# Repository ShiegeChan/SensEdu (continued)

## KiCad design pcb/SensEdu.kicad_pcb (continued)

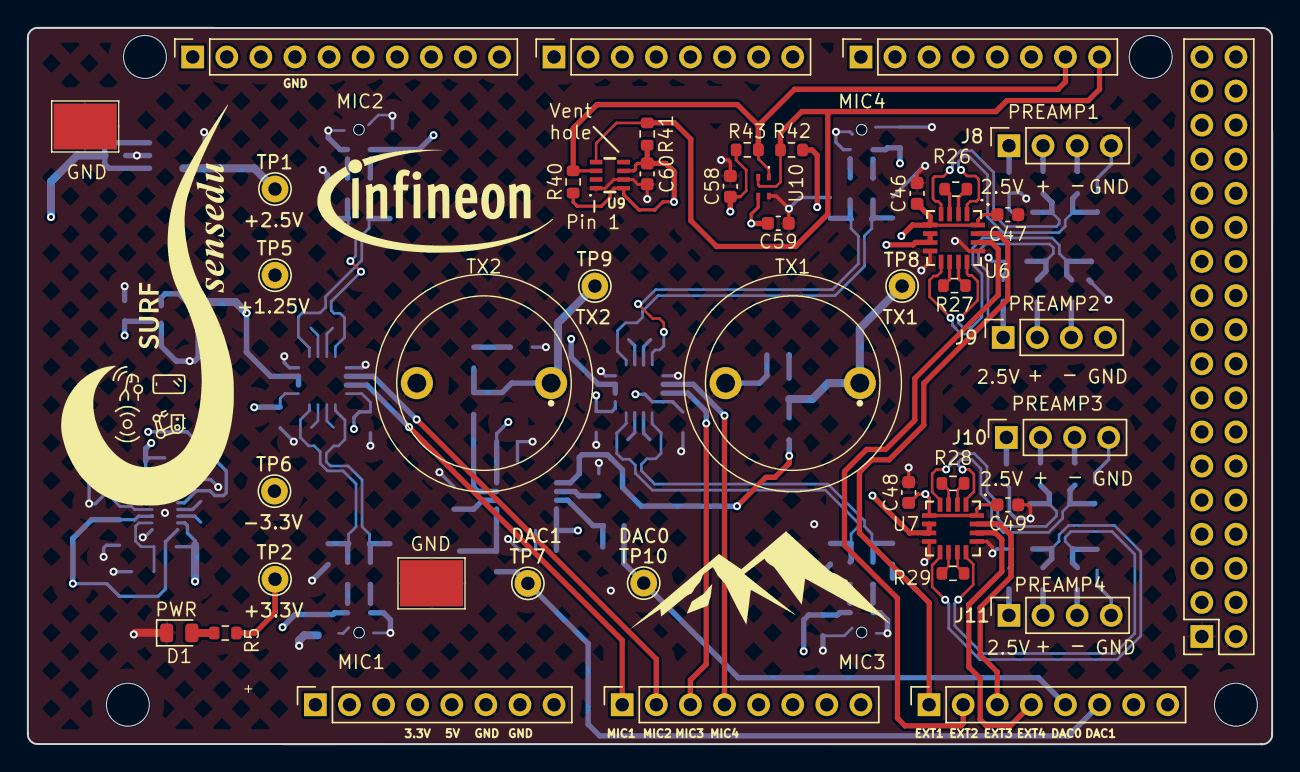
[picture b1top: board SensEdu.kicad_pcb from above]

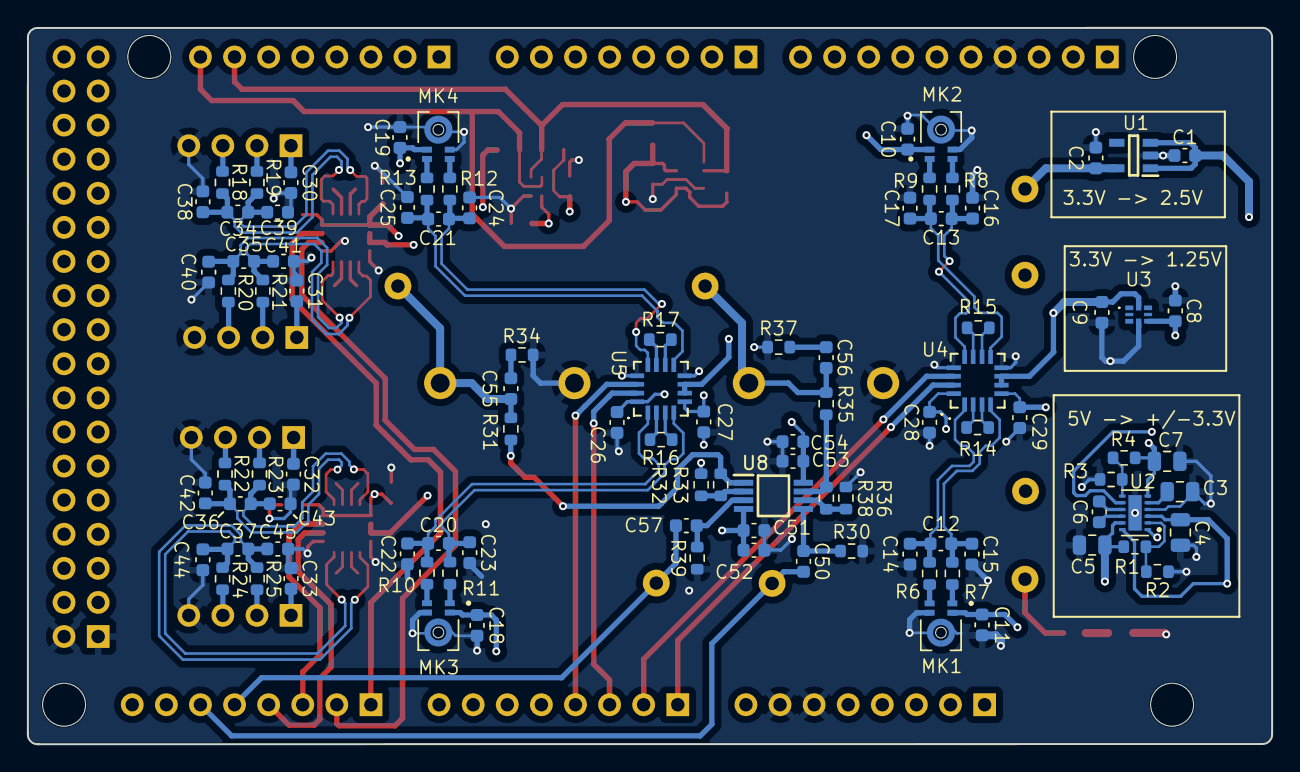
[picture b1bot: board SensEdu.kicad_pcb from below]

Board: 4 copper layers, 92.7 x 53.4 mm, 145 parts (97 on the bottom side), 83 nets.

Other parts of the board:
MH1, MH2, MH5, MH6: MountingHole_3.2mm

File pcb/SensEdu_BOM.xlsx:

Reference | Value | Footprint | Qty | DNP | Price (per 10xQty) | Total Price | Part Number | Note | Link
C1,C2,C8,C9,C26,C27,C28,C29,C46,C47,C48,C49,C51,C54 | 1u | SensEdu:C_0603_1608Metric | 14 |  | 6.5000000000000002E-2 | 0.91 | GCJ188R71E105KA01D | 10%; X7R | https://www.mouser.de/ProductDetail/Murata-Electronics/GCJ18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
C3,C4 | 4.7u | SensEdu:C_0805_2012Metric | 2 |  | 0.13300000000000001 | 0.26600000000000001 | GCJ21BR71C475KA01L | 10%; X7R | https://www.mouser.de/ProductDetail/Murata-Electronics/GCJ21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
C5,C7 | 2.2u | SensEdu:C_0805_2012Metric | 2 |  | 0.04 | 0.08 | CL21B225KAFNNNG | 10%; X7R | https://www.mouser.de/ProductDetail/Samsung-Electro-Mechanic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
C6 | 470n | SensEdu:C_0603_1608Metric | 1 |  | 5.1999999999999998E-2 | 5.1999999999999998E-2 | GRM188R71A474JA61J | 5%; X7R | https://www.mouser.de/ProductDetail/Murata-Electronics/GRM18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
C10,C11,C18,C19,C30,C31,C32,C33,C52,C53,C58,C59,C60 | 100n | SensEdu:C_0603_1608Metric | 13 |  | 5.0000000000000001E-3 | 6.5000000000000002E-2 | CL10B104JB8NNNC | 5%; X7R | https://www.mouser.de/ProductDetail/Samsung-Electro-Mechanic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
C12,C13,C20,C21,C34,C35,C36,C37 | 470p | SensEdu:C_0603_1608Metric | 8 |  | 8.3000000000000004E-2 | 0.66400000000000003 | GCM1885C2A471FA16D | 1%; C0G | https://www.mouser.de/ProductDetail/Murata-Electronics/GCM18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
C14,C15,C16,C17,C22,C23,C24,C25,C38,C39,C40,C41,C42,C43,C44,C45 | 100p | SensEdu:C_0603_1608Metric | 16 |  | 4.1000000000000002E-2 | 0.65600000000000003 | GQM1875C2E101FB12D | 2%; C0G | https://www.mouser.de/ProductDetail/Murata-Electronics/GQM18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
C50,C57 | 1n | SensEdu:C_0603_1608Metric | 2 |  | 5.1999999999999998E-2 | 0.104 | GCM1885C2A102FA16D | 1%; C0G | https://mou.sr/3Q4kneA
C55,C56 | DNI | SensEdu:C_0603_1608Metric | 2 | DNP |  | 0
D1 | LED | SensEdu:LED_0805_2012Metric | 1 |  | 0.126 | 0.126 | 598-8170-107F |  | https://www.mouser.de/ProductDetail/Dialight/598-8170-107F?q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
J1,J3,J4,J5,J6 | 1x8 Housing | SensEdu:PinSocket_1x08_P2.54mm_Vertical | 5 |  | 1.51 | 7.55 | SSQ-108-03-G-S |  | https://www.mouser.de/ProductDetail/Samtec/SSQ-108-03-G-S?qs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
J2 | 1x10 Housing | SensEdu:PinSocket_1x10_P2.54mm_Vertical | 1 |  | 2.2799999999999998 | 2.2799999999999998 | SSQ-110-03-G-S |  | https://www.mouser.de/ProductDetail/Samtec/SSQ-110-03-G-S?qs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
J7 | 2x18 Housing | SensEdu:PinSocket_2x18_P2.54mm_Vertical | 1 | DNP |  | 0
J8,J9,J10,J11 | 1x4 Housing | SensEdu:PinSocket_1x04_P2.54mm_Vertical | 4 |  | 1.1599999999999999 | 4.6399999999999997 | SSW-104-01-G-S |  | https://www.mouser.de/ProductDetail/Samtec/SSW-104-01-G-S?qs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
MK1,MK2,MK3,MK4 | IM73A135V01XTSA1 | SensEdu:MIC_IM73A135V01XTSA1 | 4 |  | 1.41 | 5.64 | IM73A135V01XTSA1 |  | https://mou.sr/4aXaWrH
R1,R4 | 130k | SensEdu:R_0603_1608Metric | 2 |  | 3.9E-2 | 7.8E-2 | ERA-3AED134V | 0.5%; 100mW; 25ppm | https://www.mouser.de/ProductDetail/Panasonic/ERA-3AED134V?q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
R2,R3 | 75k | SensEdu:R_0603_1608Metric | 2 |  | 0.17599999999999999 | 0.35199999999999998 | ERA-3APB753V | 0.1%; 100mW; 15ppm | https://www.mouser.de/ProductDetail/Panasonic/ERA-3APB753V?q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
R5 | 47 | SensEdu:R_0603_1608Metric | 1 |  | 4.5999999999999999E-2 | 4.5999999999999999E-2 | ERA-3AEB470V | 0.1%; 100mW; 25ppm | https://www.mouser.de/ProductDetail/Panasonic/ERA-3AEB470V?q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
R6,R7,R8,R9,R10,R11,R12,R13,R18,R19,R20,R21,R22,R23,R24,R25 | 3.9k | SensEdu:R_0603_1608Metric | 16 |  | 4.5999999999999999E-2 | 0.73599999999999999 | ERA-3AEB392V | 0.1%; 100mW; 25ppm | https://www.mouser.de/ProductDetail/Panasonic/ERA-3AEB392V?q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
R14,R15,R16,R17,R26,R27,R28,R29 | 1k | SensEdu:R_0603_1608Metric | 8 |  | 4.5999999999999999E-2 | 0.36799999999999999 | ERA-3AEB102V | 0.1%; 100mW; 25ppm | https://www.mouser.de/ProductDetail/Panasonic/ERA-3AEB102V?q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
R30,R39 | 43k | SensEdu:R_0603_1608Metric | 2 |  | 4.5999999999999999E-2 | 9.1999999999999998E-2 | ERA-3AEB433V | 0.1%; 100mW; 25ppm | https://mou.sr/3PpuldV
R31,R35 | 100 | SensEdu:R_0603_1608Metric | 2 |  | 6.7000000000000004E-2 | 0.13400000000000001 | ERA-3AED101V | 0.5%; 100mW; 25ppm | https://mou.sr/3xkErUr
R32,R33,R36,R38 | 22k | SensEdu:R_0603_1608Metric | 4 |  | 6.3E-2 | 0.252 | ERJ-PB3B2202V | 0.1%; 200mW; 50ppm | https://www.mouser.de/ProductDetail/Panasonic/ERJ-PB3B2202V?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
R34,R37 | DNI | SensEdu:R_0603_1608Metric | 2 | DNP |  | 0
R40,R41,R42,R43 | 10k | SensEdu:R_0603_1608Metric | 4 |  | 5.8000000000000003E-2 | 0.23200000000000001 | ERJ-PB3B1002V | 0.1%; 200mW; 50ppm | https://www.mouser.de/ProductDetail/Panasonic/ERJ-PB3B1002V?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
TP1,TP2,TP5,TP6 | Power TP | SensEdu:TestPoint_THTPad_D2.0mm_Drill1.0mm | 4 |  | 0.28699999999999998 | 1.1479999999999999 | 5000 |  | https://www.mouser.de/ProductDetail/Keystone-Electronics/500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
TP3,TP4 | GND TP | SensEdu:5018 | 2 |  | 0.28100000000000003 | 0.56200000000000006 | 5018 |  | https://mou.sr/40UKP08
TP7,TP8,TP9,TP10 | Signal TP | SensEdu:TestPoint_THTPad_D2.0mm_Drill1.0mm | 4 |  | 0.19 | 0.76 | 5001 |  | https://www.mouser.de/ProductDetail/Keystone-Electronics/500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
TX1,TX2 | 328ST16M | SensEdu:328ST16M_Speaker | 2 |  | 6.5 | 13 | 328ST16M |  | https://www.mouser.de/ProductDetail/Pro-Wave-Electronics/328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
U1 | LDLN025M25R | SensEdu:SOT95P280X145-5N | 1 |  | 0.39 | 0.39 | LDLN025M25R |  | https://www.mouser.de/ProductDetail/STMicroelectronics/LDLN0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
U2 | LM27762DSST | SensEdu:IC_LM27762DSST | 1 |  | 1.54 | 1.54 | LM27762DSST |  | https://www.mouser.de/ProductDetail/Texas-Instruments/LM2776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
U3 | TS3312AQPR | SensEdu:TS3312AQPR | 1 |  | 0.76400000000000001 | 0.76400000000000001 | TS3312AQPR |  | https://www.mouser.de/ProductDetail/STMicroelectronics/TS331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
U4,U5,U6,U7 | AD8426ACPZ-R7 | SensEdu:QFN65P400X400X100-16N | 4 |  | 5.41 | 21.64 | AD8426ACPZ-R7 |  | https://www.mouser.de/ProductDetail/Analog-Devices/AD8426ACP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
U8 | ADA4511-2ARMZ | SensEdu:SOP65P490X110-8N | 1 |  | 2.4300000000000002 | 2.4300000000000002 | ADA4511-2ARMZ |  | https://www.mouser.de/ProductDetail/Analog-Devices/ADA4511-2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
U9 | DPS368XTSA1 | SensEdu:DPS368XTSA1 | 1 |  | 2.27 | 2.27 | DPS368XTSA1 |  | https://www.mouser.de/ProductDetail/Infineon-Technologies/DP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
U10 | SHT40-AD1F-R2 | SensEdu:SHT40AD1FR2 | 1 |  | 1.56 | 1.56 | SHT40-AD1F-R2 |  | https://mou.sr/3NYpzUa
 |  |  |  |  |  | 71.387000000000015

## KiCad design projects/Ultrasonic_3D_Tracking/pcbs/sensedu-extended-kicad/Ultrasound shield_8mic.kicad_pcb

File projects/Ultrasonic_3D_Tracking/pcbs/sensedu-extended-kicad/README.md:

# Extended SensEdu Shield (8 Microphones)

> [!WARNING]
> This PCB is a messy prototype that has never been cleaned up, and it may not work at all.
> It was created for the sole purpose of quickly testing an 8-microphone setup on a very old
> SensEdu revision, and is published for reference rather than for reproduction.

If you need an 8-microphone version, please contact us and we will help you with it.

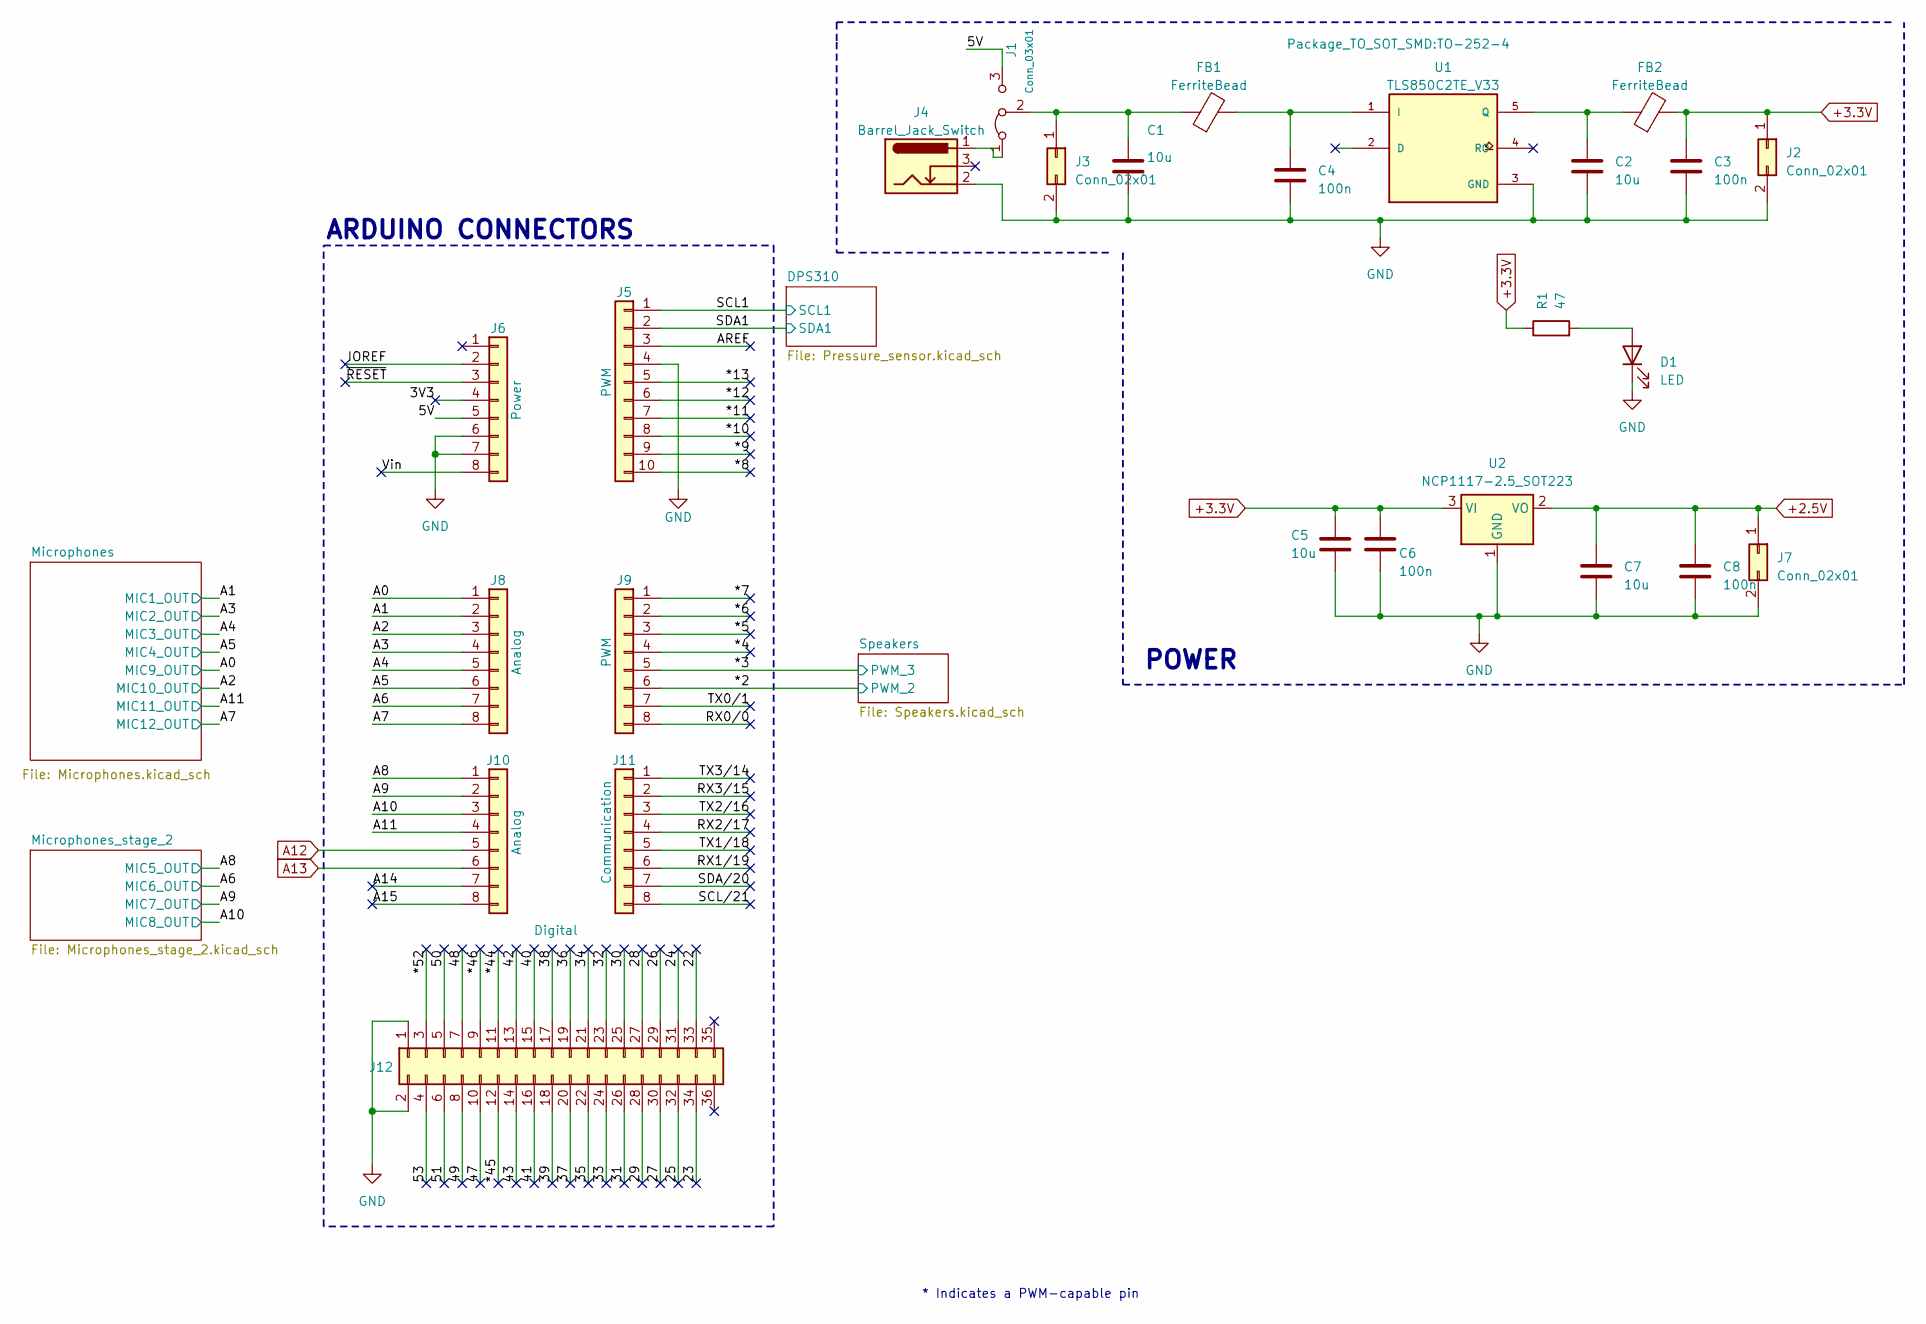
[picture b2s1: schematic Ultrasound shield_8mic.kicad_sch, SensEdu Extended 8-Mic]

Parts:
C1, C2, C5, C7: 10u; C_0805_2012Metric
C3, C4, C6, C8: 100n; C_0805_2012Metric
D1: LED; LED_0805_2012Metric
FB1, FB2: FerriteBead; L_1206_3216Metric12
J1: Conn_03x01; PinHeader_1x03_P2.54mm_Vertical
J2, J3, J7: Conn_02x01; PinSocket_1x02_P2.54mm_Vertical
J4: Barrel_Jack_Switch; BarrelJack_Wuerth_6941xx301002
J5: PWM; PinSocket_1x10_P2.54mm_Vertical
J6: Power; PinSocket_1x08_P2.54mm_Vertical
J8, J10: Analog; PinSocket_1x08_P2.54mm_Vertical
J9: PWM; PinSocket_1x08_P2.54mm_Vertical
J11: Communication; PinSocket_1x08_P2.54mm_Vertical
J12: Digital
R1: 47; R_0805_2012Metric
U1: TLS850C2TE_V33; TO-252-4
U2: NCP1117-2.5_SOT223; SOT-223-3_TabPin2

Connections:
+2.5V: C7.1, C8.1, J7.1, U2.2 (VO); also elsewhere on the board
+3.3V: C3.1, C5.1, C6.1, FB2.2, J2.1, R1.1, U2.3 (VI); also elsewhere on the board
/3V3: J6.4
/5V: J1.3 (B), J6.5
/22: J12.33
/23: J12.34
/24: J12.31
/25: J12.32
/26: J12.29
/27: J12.30
/28: J12.27
/29: J12.28
/30: J12.25
/31: J12.26
/32: J12.23
/33: J12.24
/34: J12.21
/35: J12.22
/36: J12.19
/37: J12.20
/38: J12.17
/39: J12.18
/40: J12.15
/41: J12.16
/42: J12.13
/43: J12.14
/47: J12.10
/48: J12.7
/49: J12.8
/50: J12.5
/51: J12.6
/53: J12.4
/*2: J9.6; also elsewhere on the board
/*3: J9.5; also elsewhere on the board
/*4: J9.4
/*5: J9.3
/*6: J9.2
/*7: J9.1
/*8: J5.10
/*9: J5.9
/*10: J5.8
/*11: J5.7
/*12: J5.6
/*13: J5.5
/*44: J12.11
/*45: J12.12
/*46: J12.9
/*52: J12.3
/A0: J8.1; also elsewhere on the board
/A1: J8.2; also elsewhere on the board
/A2: J8.3; also elsewhere on the board
/A3: J8.4; also elsewhere on the board
/A4: J8.5; also elsewhere on the board
/A5: J8.6; also elsewhere on the board
/A6: J8.7; also elsewhere on the board
/A7: J8.8; also elsewhere on the board
/A8: J10.1; also elsewhere on the board
/A9: J10.2; also elsewhere on the board
/A10: J10.3; also elsewhere on the board
/A11: J10.4; also elsewhere on the board
/A14: J10.7
/A15: J10.8
/AREF: J5.3
/IOREF: J6.2
/RX0/0: J9.8
/RX1/19: J11.6
/RX2/17: J11.4
/RX3/15: J11.2
/SCL1: J5.1; also elsewhere on the board
/SCL/21: J11.8
/SDA1: J5.2; also elsewhere on the board
/SDA/20: J11.7
/TX0/1: J9.7
/TX1/18: J11.5
/TX2/16: J11.3
/TX3/14: J11.1
/Vin: J6.8
/~RESET: J6.3
A12: J10.5; also elsewhere on the board
A13: J10.6; also elsewhere on the board
GND: C1.2, C2.2, C3.2, C4.2, C5.2, C6.2, C7.2, C8.2, D1.1 (K), J2.2, J3.2, J4.2, J5.4, J6.6, J6.7, J7.2, J12.1, J12.2, U1.3 (GND), U2.1 (GND); also elsewhere on the board
unnamed: D1.2 (A), R1.2
unnamed: J1.1 (A), J4.1
unnamed: C1.1, FB1.1, J1.2 (C), J3.1
unnamed: C4.1, FB1.2, U1.1 (I)
unnamed: C2.1, FB2.1, U1.5 (Q)

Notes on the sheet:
ARDUINO CONNECTORS
POWER
* Indicates a PWM-capable pin

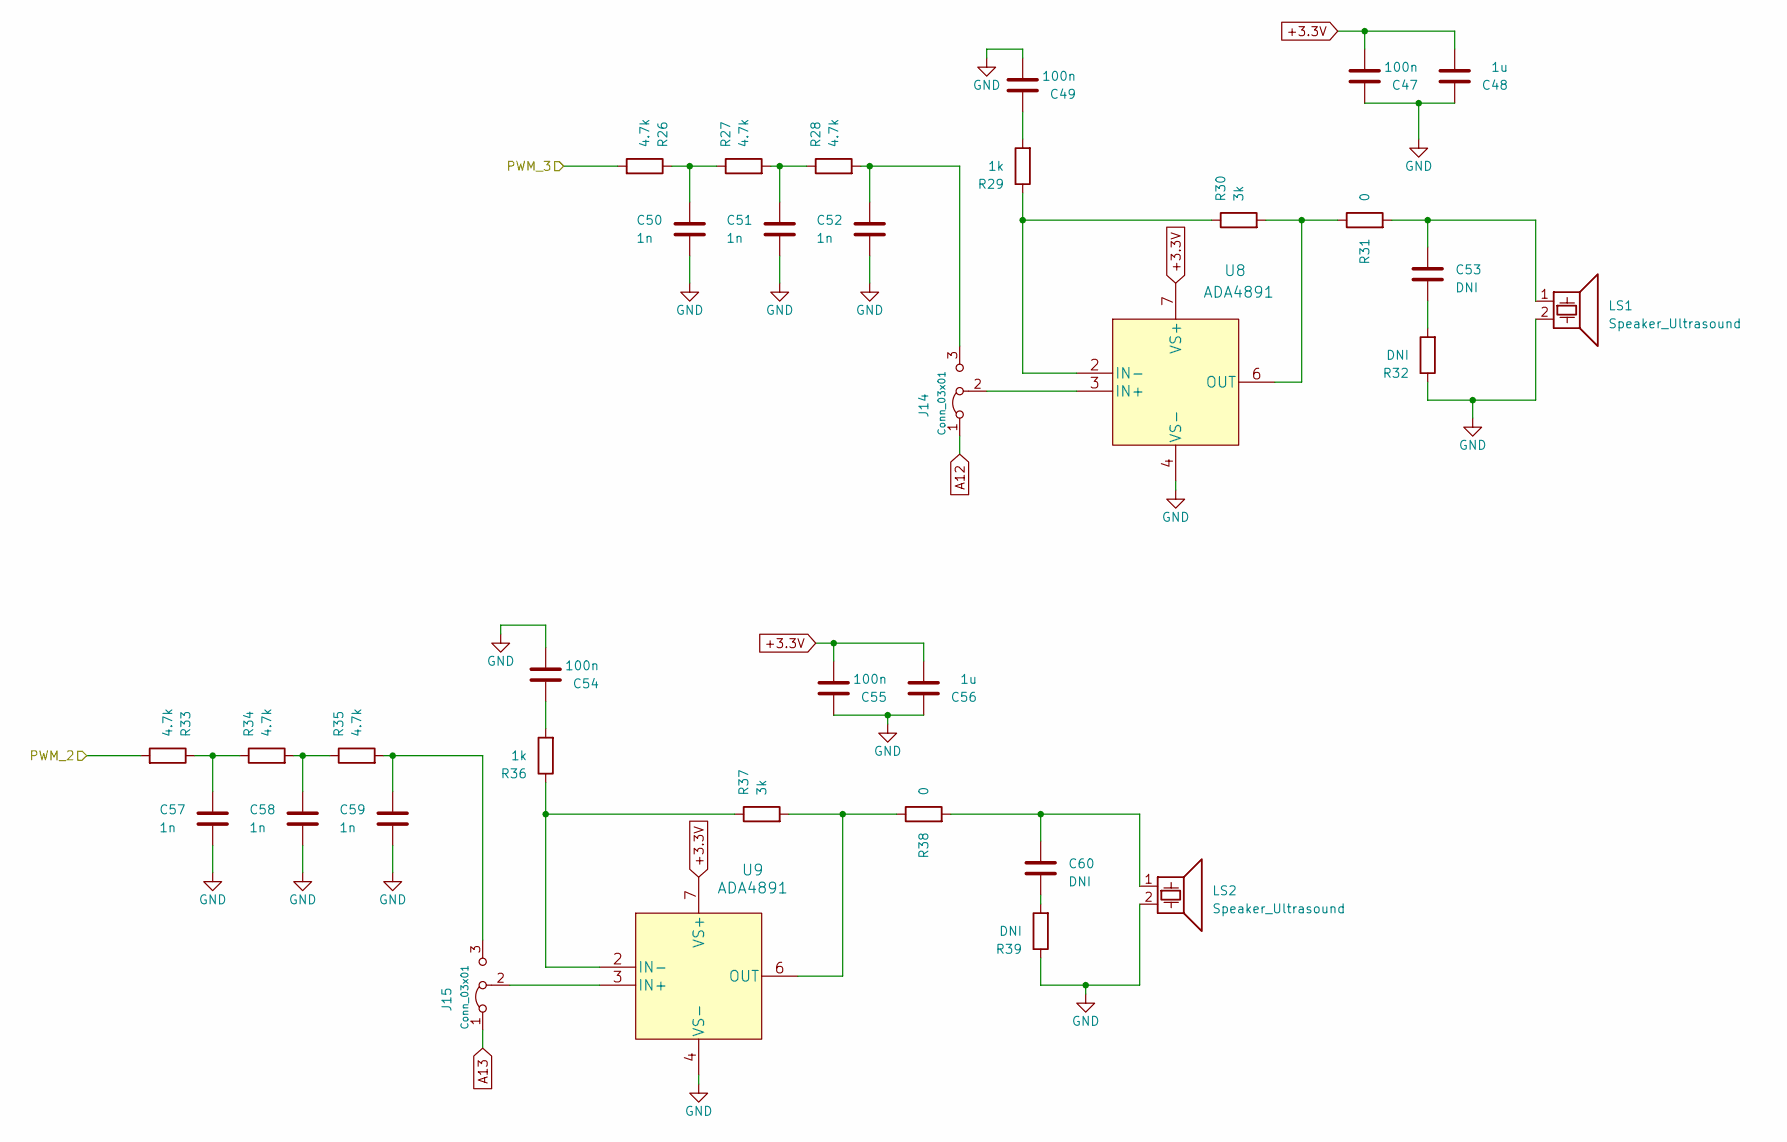
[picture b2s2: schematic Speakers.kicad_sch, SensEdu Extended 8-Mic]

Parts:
C47, C49, C54, C55: 100n; C_0805_2012Metric
C48, C56: 1u; C_0805_2012Metric
C50, C51, C52, C57, C58, C59: 1n; C_0805_2012Metric
C53, C60: DNI; C_0805_2012Metric
J14, J15: Conn_03x01; PinHeader_1x03_P2.54mm_Vertical
LS1, LS2: Speaker_Ultrasound; 328ST16M_Speaker
R26, R27, R28, R33, R34, R35: 4.7k; R_0805_2012Metric
R29, R36: 1k; R_0805_2012Metric
R30, R37: 3k; R_0805_2012Metric
R31, R38: 0; R_0805_2012Metric
R32, R39: DNI; R_0805_2012Metric
U8, U9: ADA4891; ADA4891-1ARZ

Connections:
+3.3V: C47.2, C48.2, C55.2, C56.2, U8.7 (VS+), U9.7 (VS+); also elsewhere on the board
/*2: R33.2; also elsewhere on the board
/*3: R26.2; also elsewhere on the board
A12: J14.1 (A); also elsewhere on the board
A13: J15.1 (A); also elsewhere on the board
GND: C47.1, C48.1, C49.2, C50.2, C51.2, C52.2, C54.2, C55.1, C56.1, C57.2, C58.2, C59.2, LS1.2, LS2.2, R32.1, R39.1, U8.4 (VS-), U9.4 (VS-); also elsewhere on the board
unnamed: C49.1, R29.2
unnamed: C50.1, R26.1, R27.1
unnamed: C51.1, R27.2, R28.1
unnamed: C53.1, LS1.1, R31.2
unnamed: C53.2, R32.2
unnamed: C54.1, R36.2
unnamed: C57.1, R33.1, R34.1
unnamed: C58.1, R34.2, R35.1
unnamed: C60.1, LS2.1, R38.2
unnamed: C60.2, R39.2
unnamed: C52.1, J14.3 (B), R28.2
unnamed: J14.2 (C), U8.3 (IN+)
unnamed: C59.1, J15.3 (B), R35.2
unnamed: J15.2 (C), U9.3 (IN+)
unnamed: R29.1, R30.1, U8.2 (IN-)
unnamed: R30.2, R31.1, U8.6 (OUT)
unnamed: R36.1, R37.1, U9.2 (IN-)
unnamed: R37.2, R38.1, U9.6 (OUT)

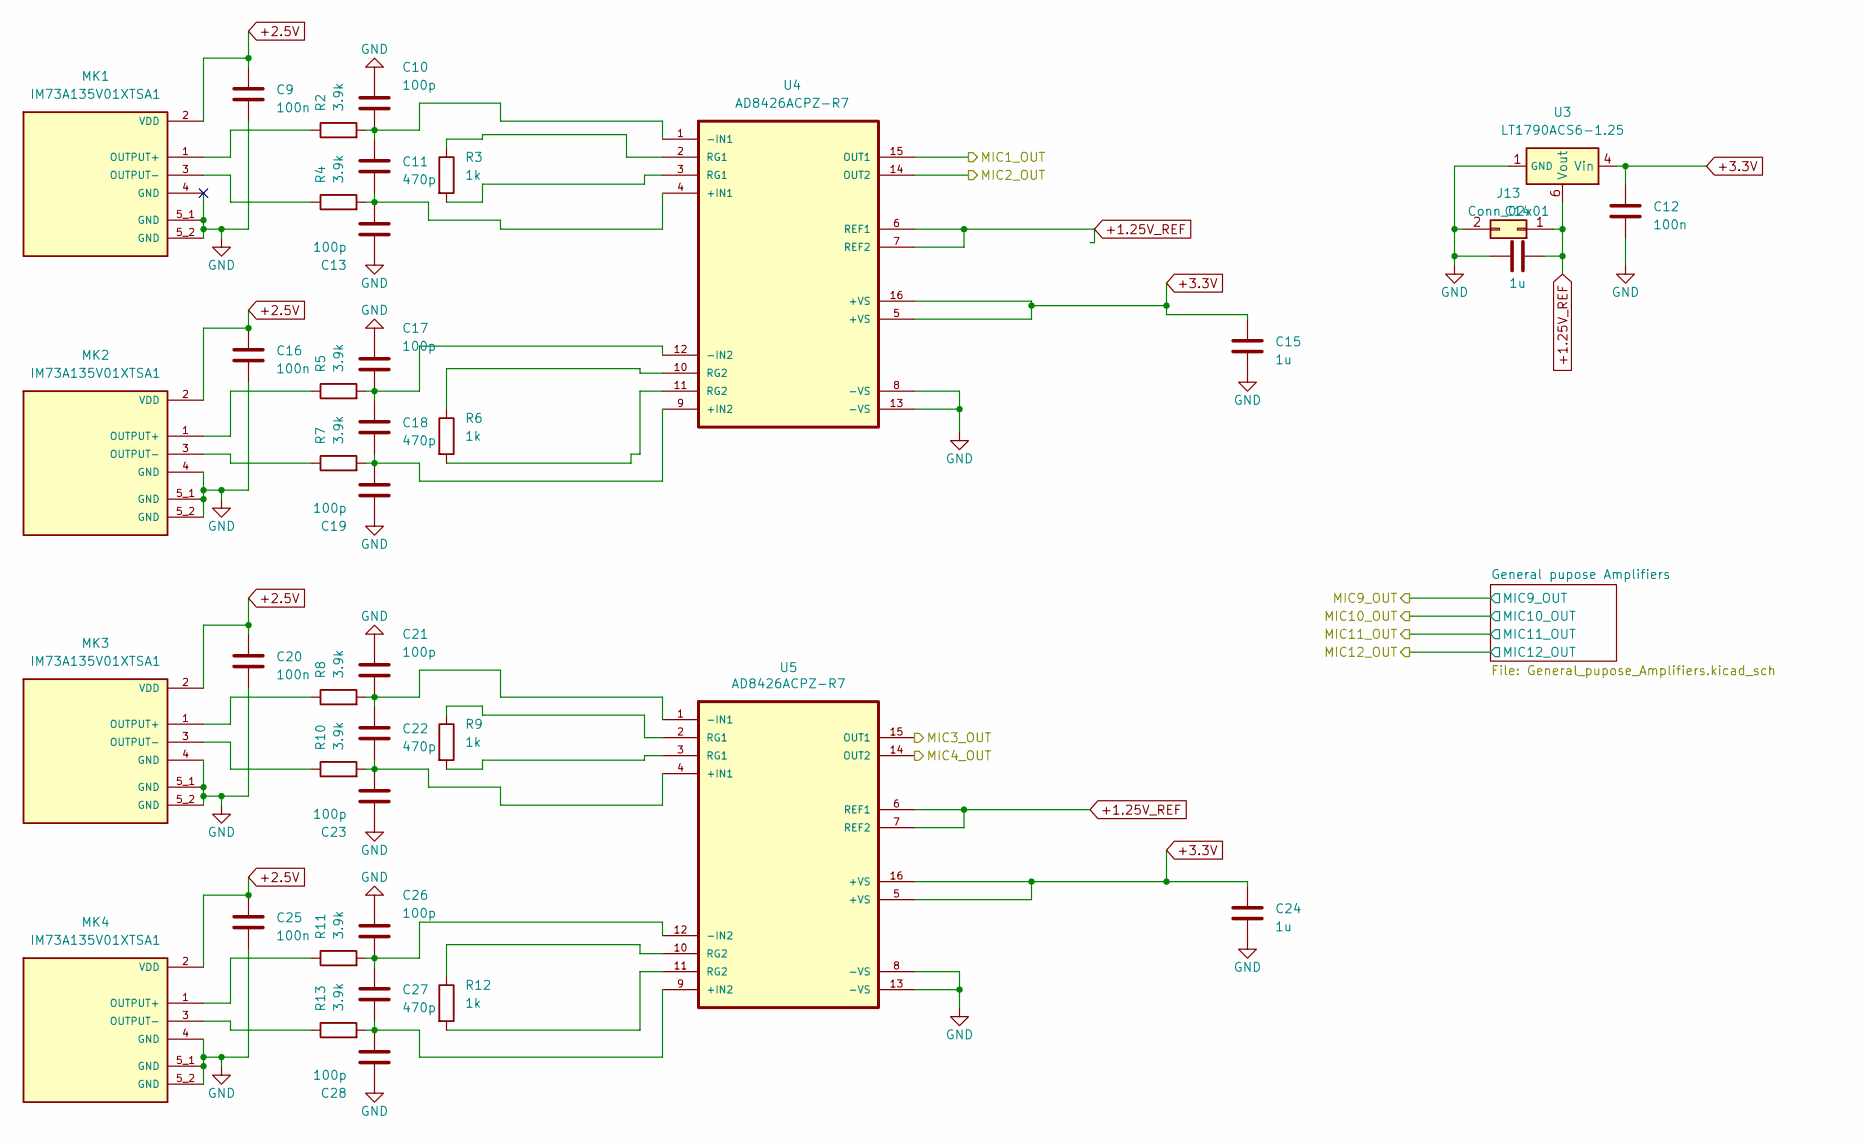
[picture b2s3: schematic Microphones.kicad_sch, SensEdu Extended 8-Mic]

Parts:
C9, C12, C16, C20, C25: 100n; C_0805_2012Metric
C10, C13, C17, C19, C21, C23, C26, C28: 100p; C_0805_2012Metric
C11, C18, C22, C27: 470p; C_0805_2012Metric
C14, C15, C24: 1u; C_0805_2012Metric
J13: Conn_02x01; PinSocket_1x02_P2.54mm_Vertical
MK1, MK2, MK3, MK4: IM73A135V01XTSA1; MIC_IM73A135V01XTSA1; PARTREV V1.20
R2, R4, R5, R7, R8, R10, R11, R13: 3.9k; R_0805_2012Metric
R3, R6, R9, R12: 1k; R_0805_2012Metric
U3: LT1790ACS6-1.25; TSOT-23-6
U4, U5: AD8426ACPZ-R7; QFN65P400X400X100-16N

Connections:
+1.25V_REF: C14.2, J13.1, U3.6 (Vout), U4.6 (REF1), U4.7 (REF2), U5.6 (REF1), U5.7 (REF2); also elsewhere on the board
+2.5V: C9.1, C16.1, C20.1, C25.1, MK1.2 (VDD), MK2.2 (VDD), MK3.2 (VDD), MK4.2 (VDD); also elsewhere on the board
+3.3V: C12.1, C15.1, C24.1, U3.4 (Vin), U4.5 (+VS), U4.16 (+VS), U5.5 (+VS), U5.16 (+VS); also elsewhere on the board
/A1: U4.15 (OUT1); also elsewhere on the board
/A3: U4.14 (OUT2); also elsewhere on the board
/A4: U5.15 (OUT1); also elsewhere on the board
/A5: U5.14 (OUT2); also elsewhere on the board
GND: C9.2, C10.1, C12.2, C13.1, C14.1, C15.2, C16.2, C17.1, C19.1, C20.2, C21.1, C23.1, C24.2, C25.2, C26.1, C28.1, J13.2, MK1.4 (GND), MK1.5_1 (GND), MK1.5_2 (GND), MK2.4 (GND), MK2.5_1 (GND), MK2.5_2 (GND), MK3.4 (GND), MK3.5_1 (GND), MK3.5_2 (GND), MK4.4 (GND), MK4.5_1 (GND), MK4.5_2 (GND), U3.1 (GND), U3.2 (GND), U4.8 (-VS), U4.13 (-VS), U5.8 (-VS), U5.13 (-VS); also elsewhere on the board
unnamed: MK1.1 (OUTPUT+), R2.1
unnamed: MK1.3 (OUTPUT-), R4.1
unnamed: MK2.1 (OUTPUT+), R5.1
unnamed: MK2.3 (OUTPUT-), R7.1
unnamed: MK3.1 (OUTPUT+), R8.1
unnamed: MK3.3 (OUTPUT-), R10.1
unnamed: MK4.1 (OUTPUT+), R11.1
unnamed: MK4.3 (OUTPUT-), R13.1
unnamed: R3.1, U4.2 (RG1)
unnamed: R3.2, U4.3 (RG1)
unnamed: R6.1, U4.10 (RG2)
unnamed: R6.2, U4.11 (RG2)
unnamed: R9.1, U5.2 (RG1)
unnamed: R9.2, U5.3 (RG1)
unnamed: R12.1, U5.10 (RG2)
unnamed: R12.2, U5.11 (RG2)
unnamed: C11.2, C13.2, R4.2, U4.4 (+IN1)
unnamed: C18.2, C19.2, R7.2, U4.9 (+IN2)
unnamed: C10.2, C11.1, R2.2, U4.1 (-IN1)
unnamed: C17.2, C18.1, R5.2, U4.12 (-IN2)
unnamed: C22.2, C23.2, R10.2, U5.4 (+IN1)
unnamed: C27.2, C28.2, R13.2, U5.9 (+IN2)
unnamed: C21.2, C22.1, R8.2, U5.1 (-IN1)
unnamed: C26.2, C27.1, R11.2, U5.12 (-IN2)

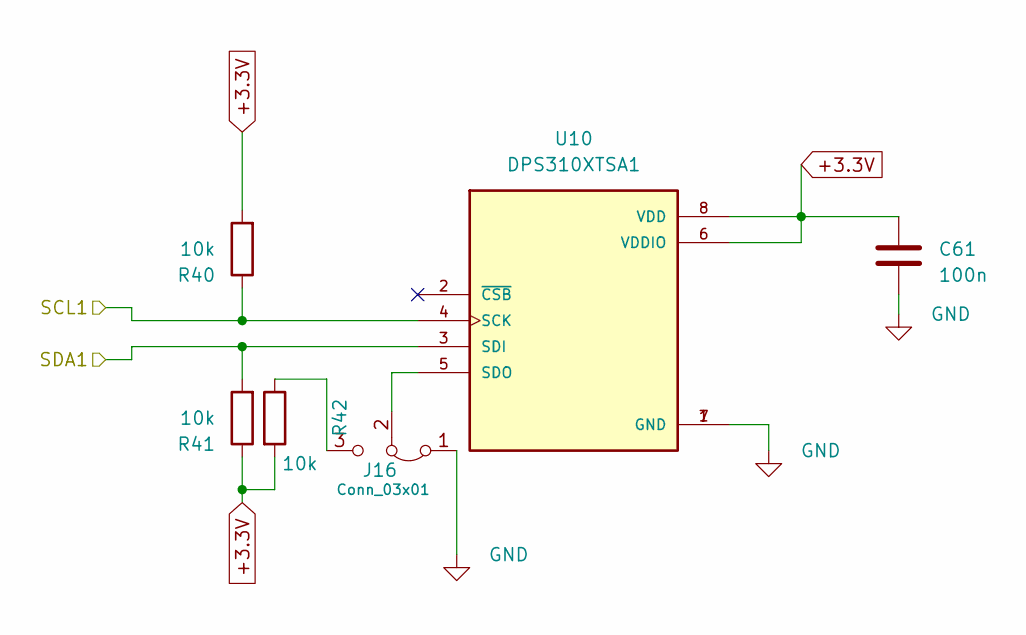
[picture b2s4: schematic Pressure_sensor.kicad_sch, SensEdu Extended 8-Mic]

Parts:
C61: 100n; C_0805_2012Metric
J16: Conn_03x01; PinHeader_1x03_P2.54mm_Vertical
R40, R41, R42: 10k; R_0805_2012Metric
U10: DPS310XTSA1; XDCR_DPS310XTSA1

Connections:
+3.3V: C61.1, R40.2, R41.1, R42.2, U10.6 (VDDIO), U10.8 (VDD); also elsewhere on the board
/SCL1: R40.1, U10.4 (SCK); also elsewhere on the board
/SDA1: R41.2, U10.3 (SDI); also elsewhere on the board
GND: C61.2, J16.1 (A), U10.1 (GND), U10.7 (GND); also elsewhere on the board
unnamed: J16.3 (B), R42.1
unnamed: J16.2 (C), U10.5 (SDO)

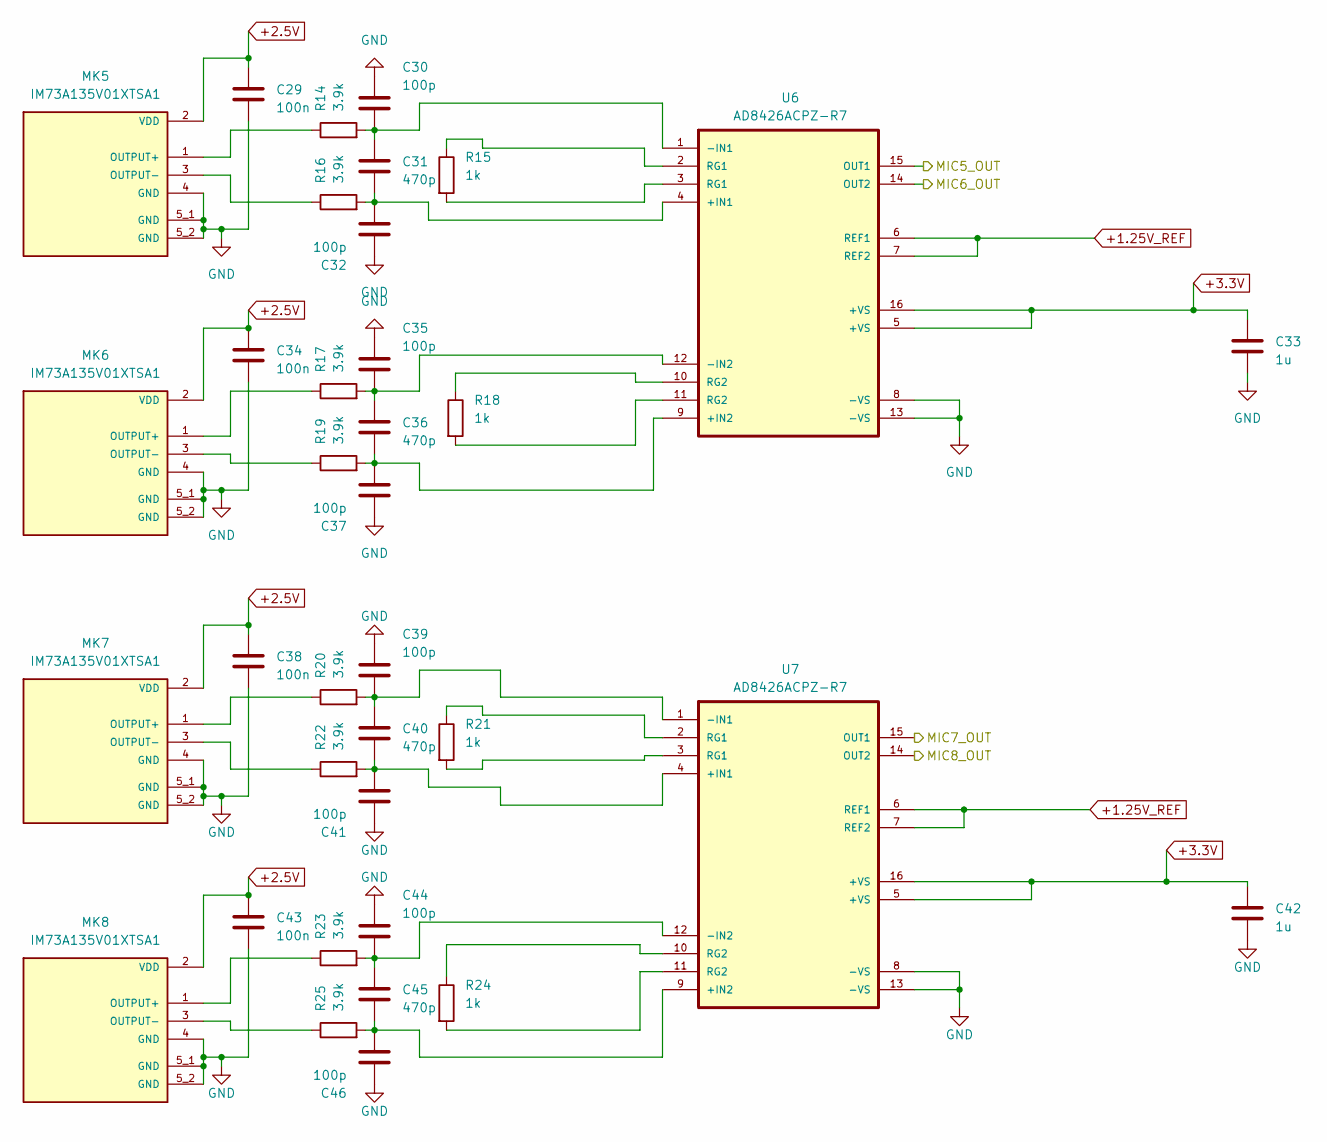
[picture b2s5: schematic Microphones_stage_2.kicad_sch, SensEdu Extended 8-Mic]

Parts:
C29, C34, C38, C43: 100n; C_0805_2012Metric
C30, C32, C35, C37, C39, C41, C44, C46: 100p; C_0805_2012Metric
C31, C36, C40, C45: 470p; C_0805_2012Metric
C33, C42: 1u; C_0805_2012Metric
MK5, MK6, MK7, MK8: IM73A135V01XTSA1; MIC_IM73A135V01XTSA1; PARTREV V1.20
R14, R16, R17, R19, R20, R22, R23, R25: 3.9k; R_0805_2012Metric
R15, R18, R21, R24: 1k; R_0805_2012Metric
U6, U7: AD8426ACPZ-R7; QFN65P400X400X100-16N

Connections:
+1.25V_REF: U6.6 (REF1), U6.7 (REF2), U7.6 (REF1), U7.7 (REF2); also elsewhere on the board
+2.5V: C29.1, C34.1, C38.1, C43.1, MK5.2 (VDD), MK6.2 (VDD), MK7.2 (VDD), MK8.2 (VDD); also elsewhere on the board
+3.3V: C33.1, C42.1, U6.5 (+VS), U6.16 (+VS), U7.5 (+VS), U7.16 (+VS); also elsewhere on the board
/A6: U6.14 (OUT2); also elsewhere on the board
/A8: U6.15 (OUT1); also elsewhere on the board
/A9: U7.15 (OUT1); also elsewhere on the board
/A10: U7.14 (OUT2); also elsewhere on the board
GND: C29.2, C30.1, C32.1, C33.2, C34.2, C35.1, C37.1, C38.2, C39.1, C41.1, C42.2, C43.2, C44.1, C46.1, MK5.4 (GND), MK5.5_1 (GND), MK5.5_2 (GND), MK6.4 (GND), MK6.5_1 (GND), MK6.5_2 (GND), MK7.4 (GND), MK7.5_1 (GND), MK7.5_2 (GND), MK8.4 (GND), MK8.5_1 (GND), MK8.5_2 (GND), U6.8 (-VS), U6.13 (-VS), U7.8 (-VS), U7.13 (-VS); also elsewhere on the board
unnamed: MK5.1 (OUTPUT+), R14.1
unnamed: MK5.3 (OUTPUT-), R16.1
unnamed: MK6.1 (OUTPUT+), R17.1
unnamed: MK6.3 (OUTPUT-), R19.1
unnamed: MK7.1 (OUTPUT+), R20.1
unnamed: MK7.3 (OUTPUT-), R22.1
unnamed: MK8.1 (OUTPUT+), R23.1
unnamed: MK8.3 (OUTPUT-), R25.1
unnamed: R15.1, U6.2 (RG1)
unnamed: R15.2, U6.3 (RG1)
unnamed: R18.1, U6.10 (RG2)
unnamed: R18.2, U6.11 (RG2)
unnamed: R21.1, U7.2 (RG1)
unnamed: R21.2, U7.3 (RG1)
unnamed: R24.1, U7.10 (RG2)
unnamed: R24.2, U7.11 (RG2)
unnamed: C31.2, C32.2, R16.2, U6.4 (+IN1)
unnamed: C36.2, C37.2, R19.2, U6.9 (+IN2)
unnamed: C30.2, C31.1, R14.2, U6.1 (-IN1)
unnamed: C35.2, C36.1, R17.2, U6.12 (-IN2)
unnamed: C40.2, C41.2, R22.2, U7.4 (+IN1)
unnamed: C45.2, C46.2, R25.2, U7.9 (+IN2)
unnamed: C39.2, C40.1, R20.2, U7.1 (-IN1)
unnamed: C44.2, C45.1, R23.2, U7.12 (-IN2)

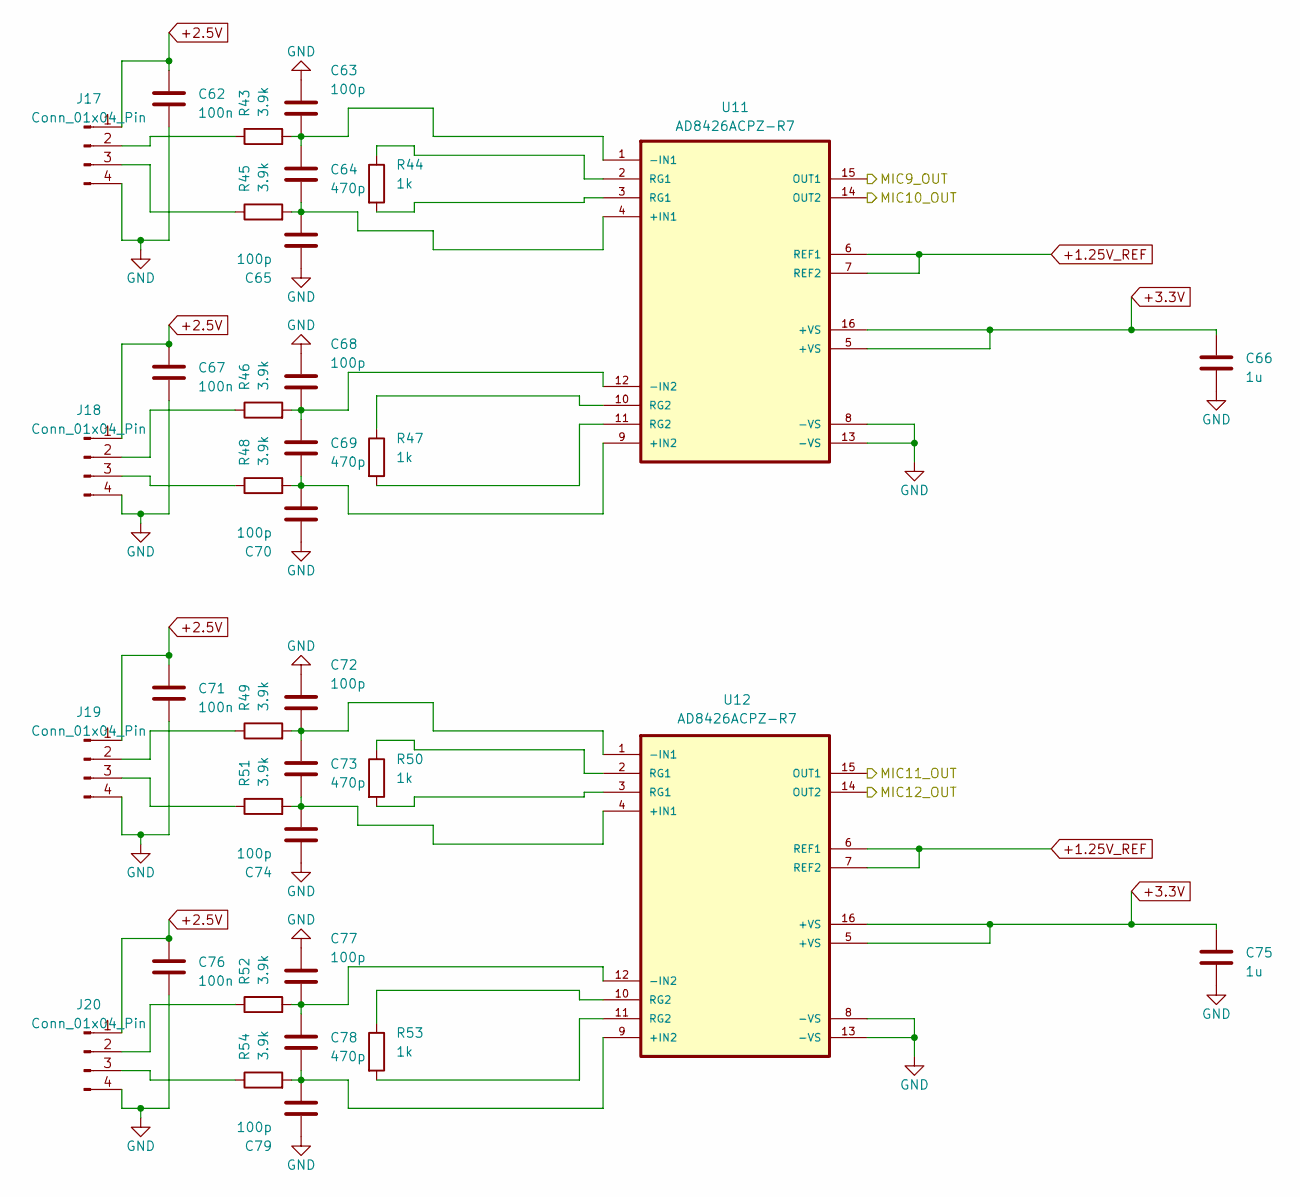
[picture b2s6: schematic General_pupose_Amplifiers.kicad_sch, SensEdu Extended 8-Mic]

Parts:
C62, C67, C71, C76: 100n; C_0805_2012Metric
C63, C65, C68, C70, C72, C74, C77, C79: 100p; C_0805_2012Metric
C64, C69, C73, C78: 470p; C_0805_2012Metric
C66, C75: 1u; C_0805_2012Metric
J17, J18, J19, J20: Conn_01x04_Pin; PinSocket_1x04_P2.54mm_Vertical
R43, R45, R46, R48, R49, R51, R52, R54: 3.9k; R_0805_2012Metric
R44, R47, R50, R53: 1k; R_0805_2012Metric
U11, U12: AD8426ACPZ-R7; QFN65P400X400X100-16N

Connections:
+1.25V_REF: U11.6 (REF1), U11.7 (REF2), U12.6 (REF1), U12.7 (REF2); also elsewhere on the board
+2.5V: C62.1, C67.1, C71.1, C76.1, J17.1, J18.1, J19.1, J20.1; also elsewhere on the board
+3.3V: C66.1, C75.1, U11.5 (+VS), U11.16 (+VS), U12.5 (+VS), U12.16 (+VS); also elsewhere on the board
/A0: U11.15 (OUT1); also elsewhere on the board
/A2: U11.14 (OUT2); also elsewhere on the board
/A7: U12.14 (OUT2); also elsewhere on the board
/A11: U12.15 (OUT1); also elsewhere on the board
GND: C62.2, C63.1, C65.1, C66.2, C67.2, C68.1, C70.1, C71.2, C72.1, C74.1, C75.2, C76.2, C77.1, C79.1, J17.4, J18.4, J19.4, J20.4, U11.8 (-VS), U11.13 (-VS), U12.8 (-VS), U12.13 (-VS); also elsewhere on the board
unnamed: J17.2, R43.1
unnamed: J17.3, R45.1
unnamed: J18.2, R46.1
unnamed: J18.3, R48.1
unnamed: J19.2, R49.1
unnamed: J19.3, R51.1
unnamed: J20.2, R52.1
unnamed: J20.3, R54.1
unnamed: R44.1, U11.2 (RG1)
unnamed: R44.2, U11.3 (RG1)
unnamed: R47.1, U11.10 (RG2)
unnamed: R47.2, U11.11 (RG2)
unnamed: R50.1, U12.2 (RG1)
unnamed: R50.2, U12.3 (RG1)
unnamed: R53.1, U12.10 (RG2)
unnamed: R53.2, U12.11 (RG2)
unnamed: C64.2, C65.2, R45.2, U11.4 (+IN1)
unnamed: C69.2, C70.2, R48.2, U11.9 (+IN2)
unnamed: C63.2, C64.1, R43.2, U11.1 (-IN1)
unnamed: C68.2, C69.1, R46.2, U11.12 (-IN2)
unnamed: C73.2, C74.2, R51.2, U12.4 (+IN1)
unnamed: C78.2, C79.2, R54.2, U12.9 (+IN2)
unnamed: C72.2, C73.1, R49.2, U12.1 (-IN1)
unnamed: C77.2, C78.1, R52.2, U12.12 (-IN2)
